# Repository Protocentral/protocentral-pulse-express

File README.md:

Protocentral Pulse Express with MAX30102 and MAX32664D
================================

## Don't have one? [Buy it here](https://protocentral.com/product/pulse-express-pulse-ox-heart-rate-sensor-with-max32664/)

Pulse Express is a compact breakout that pairs a high-sensitivity MAX30102 optical
sensor with a MAX32664D biometric sensor hub. The MAX32664D runs Maxim/ADI's
on-chip Blood-Pressure-Trending (BPT) algorithm and reports calculated heart rate,
SpO2 and blood-pressure-trend data over I2C, so the host MCU does no signal
processing. Suitable for finger-based wearable health R&D.

> **Note:** This device is for research & development only and is **NOT** a medical
> device. It is not FDA, CE or FCC approved for consumer use.

## Overview

**Key capabilities (all exposed by this library):**
- Raw PPG streaming (IR + Red, 24-bit ADC counts)
- Heart rate and SpO2 with per-reading confidence
- Blood-pressure trending — calibration → estimation (systolic / diastolic)
- SpO2 coefficient calibration (per Maxim AN6845)
- Multi-subject calibration, up to 5 subjects (firmware >= 40.5.0)
- Heart-rate variability (SDNN / RMSSD) from inter-beat intervals
- Runtime firmware-version detection and capability adaptation (40.x line)
- Factory / recovery firmware flasher for the MAX32664 bootloader

## Installation

**Arduino Library Manager (recommended):** search for *ProtoCentral Pulse Express*
and click Install.

**Manual:** download this repository as a ZIP and use
*Sketch -> Include Library -> Add .ZIP Library...* in the Arduino IDE.

## Hardware Setup

| MAX32664 pin | Arduino UNO / R4 | ESP32 (example) | Function          |
|--------------|------------------|-----------------|-------------------|
| SDA          | A4               | GPIO21          | I2C data          |
| SCL          | A5               | GPIO22          | I2C clock         |
| Vin          | 5V               | 5V / VIN        | Power             |
| GND          | GND              | GND             | Ground            |
| MFIO         | D2               | any GPIO        | Data-ready / mode |
| RESET        | D4               | any GPIO        | Hub reset         |

The RESET and MFIO pins are passed to the constructor, so any GPIOs work.

## Quick Start

```cpp
#include <Wire.h>
#include "protocentral_pulse_express.h"

PulseExpress hub(/*RESET=*/4, /*MFIO=*/2);

void setup() {
  Serial.begin(57600);
  Wire.begin();
  if (hub.begin() != PulseExpressStatus::Ok) { /* handle error */ }
  hub.startEstimation();                 // streams HR + SpO2 (BP needs calibration)
}

void loop() {
  PulseExpressSample s[8];
  size_t n = 0;
  if (hub.readSamples(s, 8, &n) == PulseExpressStatus::Ok)
    for (size_t i = 0; i < n; ++i) {
      Serial.print("HR ");    Serial.print(s[i].heartRate(), 1);
      Serial.print(" SpO2 "); Serial.println(s[i].spo2(), 1);
    }
}
```

## Firmware versions & capabilities

The MAX32664D changed its protocol across the 40.x firmware line. `begin()` reads
the hub firmware version and derives a capability set (`hub.caps()`); the driver
then adapts automatically. Notable breakpoints:

- **40.2.2+** — BP-medication / rest-mode setup steps dropped.
- **40.5.0+** — calibration vector 824 -> 512 bytes, sample 23 -> 29 bytes, date
  format YYMMDD -> YYYYMMDD, and multi-point calibration (`calIndex` 0..4).

Branch on `hub.caps().multiPointCalib` if you support both. Version checking is a
**soft warning**: `begin()` still proceeds on unexpected firmware and reports it via
`hub.firmwareSupported()`.

**Firmware is pre-installed at the factory.** Boards ship flashed and ready; you do
not need a firmware image for normal use. The MAX32664D application image (`.msbl`)
is Maxim/ADI IP and is **not** redistributed here. Re-flashing is a factory/recovery
operation — see [`examples/11.FirmwareFlash`](examples/11.FirmwareFlash) and
[`extras/`](extras/).

## Examples

| #  | Sketch | Shows |
|----|--------|-------|
| 01 | RawPPGStreamPlotter       | Raw IR PPG to Arduino Serial Plotter |
| 02 | RawPPGStreamOpenView      | Raw IR/Red to ProtoCentral OpenView GUI |
| 03 | HeartRateSpO2             | Live heart rate + SpO2 (no calibration) |
| 04 | BPTCalibration            | Run BPT calibration, dump the vector |
| 05 | BPTEstimation             | Estimate BP/HR/SpO2 from a saved vector |
| 06 | BPTCalibrateAndEstimate   | Full calibrate -> estimate, end to end |
| 07 | SaveLoadCalibrationEEPROM | Persist the vector to EEPROM, reload on boot |
| 08 | MultiSubjectCalibration   | Calibrate up to 5 subjects (FW >= 40.5.0) |
| 09 | HeartRateVariability      | SDNN / RMSSD from inter-beat intervals |
| 10 | DeviceInfoAndDiagnostics  | Firmware versions, caps, live hub status |
| 11 | FirmwareFlash             | Factory/recovery .msbl flasher |

## Hub firmware flashing (factory / recovery)

Boards ship pre-flashed — you normally never need this. To recover a hub or
change its MAX32664D firmware version, [`flash-firmware.sh`](flash-firmware.sh)
uploads the [`11.FirmwareFlash`](examples/11.FirmwareFlash) relay sketch and then
streams your `.msbl` to it:

```bash
./flash-firmware.sh --dry-run  extras/firmware/<image>.msbl   # parse only
./flash-firmware.sh --esp32 --port <PORT> extras/firmware/<image>.msbl
```

**Host board:** a page write is one 8210-byte I2C transaction, so the host's Wire
buffer must hold all of it — use an **ESP32 or RP2040**. The UNO R4 cannot flash
(its Renesas Wire caps transactions at 255 bytes); the tool detects this and
stops before erasing anything.

The `.msbl` is Maxim/ADI IP and is not distributed with this library; supply your
own. Full usage, the manual two-command path, and troubleshooting are in
[`extras/flash_tool/README.md`](extras/flash_tool/README.md).

## API Reference

Construct with the reset and MFIO pins (and optionally a `TwoWire` bus):
`PulseExpress hub(resetPin, mfioPin, Wire);`

- `begin()` — reset hub, enter application mode, read version, derive caps.
- `version()`, `algoVersion()`, `caps()`, `firmwareSupported()` — device info.
- BPT calibration: `startCalibration(...)`, `readSample(...)`, `readCalibrationVector(...)`.
- BPT estimation: `loadCalibrationVector(...)`, `startEstimation(...)`, `readSamples(...)`.
- Raw PPG: `startRaw()`, `readRaw(...)`.
- Diagnostics / teardown: `readStatus(...)`, `stop()`.

All fallible calls return `PulseExpressStatus`; compare against
`PulseExpressStatus::Ok`. See [`src/protocentral_pulse_express.h`](src/protocentral_pulse_express.h)
for the full documented API.

> **Migrating from 2.0.x:** the class was `Max32664` with `Max32664*` types. Those
> names still work via `#include "max32664.h"`. New code should use `PulseExpress`
> and `#include "protocentral_pulse_express.h"`. See [CHANGELOG.md](CHANGELOG.md).

## For further details

Refer to [the Pulse Express documentation](https://docs.protocentral.com/getting-started-with-PulseExpress).

License Information
===================

This product is open source! Both our hardware and software are open source and
licensed under the following licenses:

**Hardware** — [CERN-OHL-P v2](https://ohwr.org/cern_ohl_p_v2.txt). Copyright CERN 2020.

**Software** — [MIT License](http://opensource.org/licenses/MIT).

**Documentation** — [Creative Commons Share-alike 4.0 International](http://creativecommons.org/licenses/by-sa/4.0/).

See [*LICENSE.md*](LICENSE.md) for the detailed license descriptions.

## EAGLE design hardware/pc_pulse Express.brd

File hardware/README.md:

# Hardware — earlier revision (archived)

The Eagle design files in this folder (`pc_pulse Express.sch`,
`pc_pulse Express.brd`, `pc_pulse express_schematic.pdf`) are an earlier
revision of the ProtoCentral Pulse Express board.

They are kept here permanently so that existing links, forks, and references to
these files continue to work. They are no longer the current design.

## Current design files

Revision **v3** and everything that follows it live in a dedicated hardware
repository, as a KiCad project:

**https://github.com/Protocentral/protocentral_pulse_express_hardware**

| | |
|---|---|
| v3 schematic (PDF) | [protocentral-pulse-express-v3-schematic.pdf](https://github.com/Protocentral/protocentral_pulse_express_hardware/blob/main/hardware/protocentral-pulse-express-v3-schematic.pdf) |
| v3 KiCad project | [`hardware/`](https://github.com/Protocentral/protocentral_pulse_express_hardware/tree/main/hardware) |
| Product page | https://protocentral.com/product/pulse-express-pulse-ox-heart-rate-sensor-with-max32664/ |

This repository remains the home of the **Arduino library** for Pulse Express.
Only the hardware design files have moved.

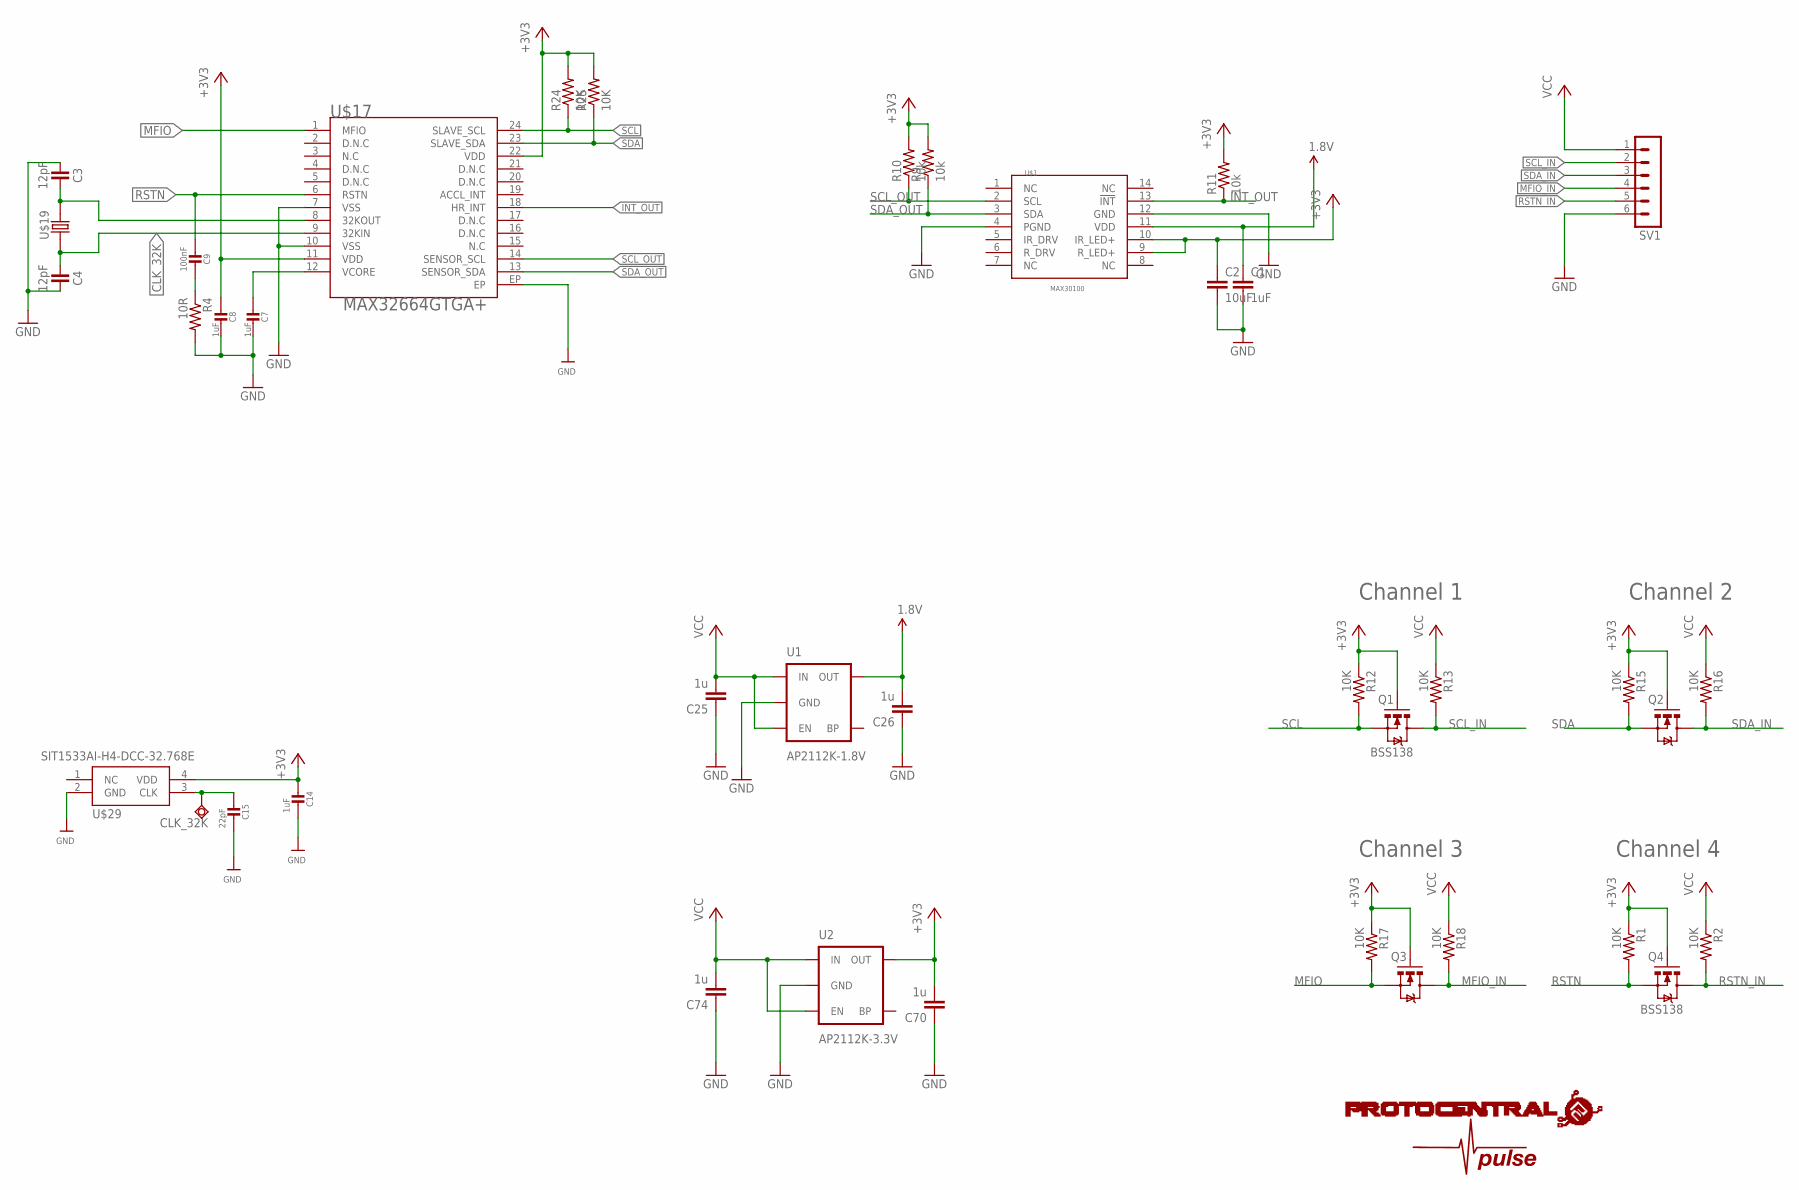
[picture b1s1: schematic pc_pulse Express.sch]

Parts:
C1: 1uF; C0402
C2: 10uF; C0402
C3, C4: 12pF; C0402
C7, C8, C14: 1uF; _0402
C9: 100nF; _0402
C15: 22pF; _0402
C25, C26, C70, C74: 1u; C0402
Q1, Q2, Q3, Q4: BSS138; SOT23-3
R1, R2, R12, R13, R15, R16, R17, R18, R24, R25: 10K; 0402-RES
R4: 10R; 0402-RES
R9, R10, R11: 10k; R0402
SV1: MA06-1
SWIO1: TPSQTP11R; TP11R
U1: AP2112K-1.8V; SOT23-5
U2: AP2112K-3.3V; SOT23-5
U$1: MAX30100; OESIP-14
U$3: PROTY_LOGO_WITH_TEXT; PROTY_WITH_TEXT
U$4: PULSE; PULSESMALL
U$17: MAX32664GTGA+; TQFN-24L
U$19: 520-327-12.5-34B(32.768KHZ); ECX-31B
U$29: SIT1533AI-H4-DCC-32.768E; SIT1533

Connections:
1.8V: C1.1, C26.2, U1.5 (OUT), U$1.11 (VDD)
+3V3: C2.1, C8.1, C14.1, C70.2, Q1.1 (G), Q2.1 (G), Q3.1 (G), Q4.1 (G), R1.1, R9.2, R10.2, R11.2, R12.1, R15.1, R17.1, R24.2, R25.2, U2.5 (OUT), U$1.9 (R_LED+), U$1.10 (IR_LED+), U$17.11 (VDD), U$17.22 (VDD), U$29.4 (VDD)
CLK_32K: C4.1, C15.1, SWIO1.TP, U$17.9 (32KIN), U$19.P$1 (1), U$29.3 (CLK)
GND: C1.2, C2.2, C3.1, C4.2, C7.2, C8.2, C14.2, C15.2, C25.1, C26.1, C70.1, C74.1, R4.2, SV1.6, U1.2 (GND), U2.2 (GND), U$1.4 (PGND), U$1.12 (GND), U$17.7 (VSS), U$17.10 (VSS), U$17.EP, U$29.2 (GND)
INT_OUT: R11.1, U$1.13 (!INT), U$17.18 (HR_INT)
MFIO: Q3.2 (S), R17.2, U$17.1 (MFIO)
MFIO_IN: Q3.3 (D), R18.2, SV1.4
unnamed: C7.1, U$17.12 (VCORE)
unnamed: C9.2, R4.1
unnamed: C3.2, U$17.8 (32KOUT), U$19.P$2 (2)
RSTN: C9.1, Q4.2 (S), R1.2, U$17.6 (RSTN)
RSTN_IN: Q4.3 (D), R2.2, SV1.5
SCL: Q1.2 (S), R12.2, R24.1, U$17.24 (SLAVE_SCL)
SCL_IN: Q1.3 (D), R13.2, SV1.2
SCL_OUT: R10.1, U$1.2 (SCL), U$17.14 (SENSOR_SCL)
SDA: Q2.2 (S), R15.2, R25.1, U$17.23 (SLAVE_SDA)
SDA_IN: Q2.3 (D), R16.2, SV1.3
SDA_OUT: R9.1, U$1.3 (SDA), U$17.13 (SENSOR_SDA)
VCC: C25.2, C74.2, R2.1, R13.1, R16.1, R18.1, SV1.1, U1.1 (IN), U1.3 (EN), U2.1 (IN), U2.3 (EN)

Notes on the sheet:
Channel 1
Channel 2
Channel 3
Channel 4

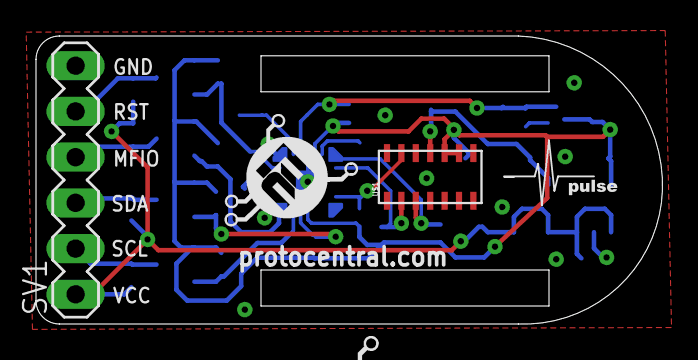
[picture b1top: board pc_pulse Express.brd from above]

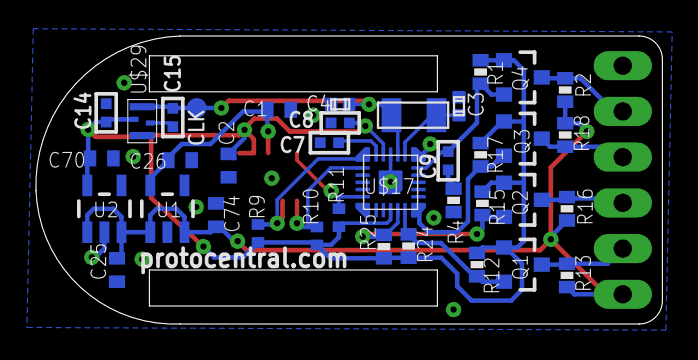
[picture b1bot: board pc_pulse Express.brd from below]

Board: 4 copper layers, 34.8 x 16.0 mm, 42 parts (37 on the bottom side), 19 nets.

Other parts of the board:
U$5: PROTY-LOGO; LOGO-PROTY@1

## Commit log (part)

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2020-09-25 basic code for max32664, not tested
2020-09-25 read samples
2020-12-10 raw mode working, algo mode not tested
2020-12-10 minor fix in raw mode
2020-12-11 disabled calibration procedure
2020-12-11 made basic algo readings working
2020-12-11 small edits on algo mode
2020-12-11 bug fix
2020-12-11 made it into library format
2020-12-12 organised the code
2020-12-12 Fixed return type issue for Arduino mbed compatibility
2020-12-15 added more configuration functions
2020-12-16 Update Arduino library format
2020-12-16 bug fix on raw mode
2020-12-16 Fix ambiguous declaration errors
2020-12-16 Updated library file
2020-12-30 added openview example
2020-12-30 changed buffer length
2020-12-31 Added hardware files
2021-03-27 Update license information
2024-03-21 Changed data format and sample size
2024-10-17 images updated and schematic reoragnized
2024-10-22 documentation link updated
2024-11-25 Removed delay for the openview code
2026-04-28 Migrate to new AP. Add multi-version support
2026-04-28 Increased all command delays
2026-06-17 Modernize to v2.1.0: PulseExpress API, expanded examples, bootloader
    - Rename driver class Max32664 -> PulseExpress and types Max32664* ->
    PulseExpress*; old names kept via max32664.h compatibility shim. Rename
    sources to protocentral_pulse_express.{h,cpp}. SPDX headers throughout.
    - Fix earlier-firmware regression: begin() no longer hard-fails on non-40.x
    hubs; version check is now a soft warning exposed via firmwareSupported().
    - Fix raw PPG streaming data loss: drain FIFO with a short read delay,

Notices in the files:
README.md:
License: MIT
parts and their libraries:
SparkFun-PowerIC: Licensing: Creative Commons ShareAlike 4.0 International - https://creativecommons.org/licenses/by-sa/4.0
microbuilder: This work is placed in the public domain, and may be freely used for commercial and non-commercial work with the following conditions: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
